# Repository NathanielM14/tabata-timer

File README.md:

tabata-timer-module
***
**Personal Project Description**:

This Tabata Timer Module is used to program calisthenics and any other static/dynamic exercises that are to be done in a specific time interval. The purpose of this timer is to show exercise time, resting time, and sets utilizing finite state machine logic. The module includes 5 fully customizable profiles that are written to the EEPROM to allow for multi-profile saving. Buzzer alerts are given nearing the end of each state to notify user of when they have reached the set amount of time. All components are through-hole and were soldered to the PCB board (Note a simple soldering iron will be required to solder all the through-hole components). Files and descriptions are listed below in the table along with all the required parts for the project.

**Files**:

| File | Description |
| ------- | --------- |
| tabata.kicad_sch | Schematic |
| SSD1306.pretty | SSD1306 Footprint | 
| tabata.kicad_pcb | PCB | 
| tabata_v1.ino | Program |

**Parts List**:
* (1x) 128x64 4-pin SSD1306 OLED (I2C)
* (1x) 5641AS (common anode)
* (4x) Push Button
* (1x) Arduino NANO / NON-OEM equivalent
* (4x) 10kΩ Resistors
* (7x) 220Ω Resistors
* (1x) 330Ω Resistors
* (1x) Passive Buzzer

1.**Schematic**

2. **SSD1306 Footprint**

3. **PCB**

4. **Physical**

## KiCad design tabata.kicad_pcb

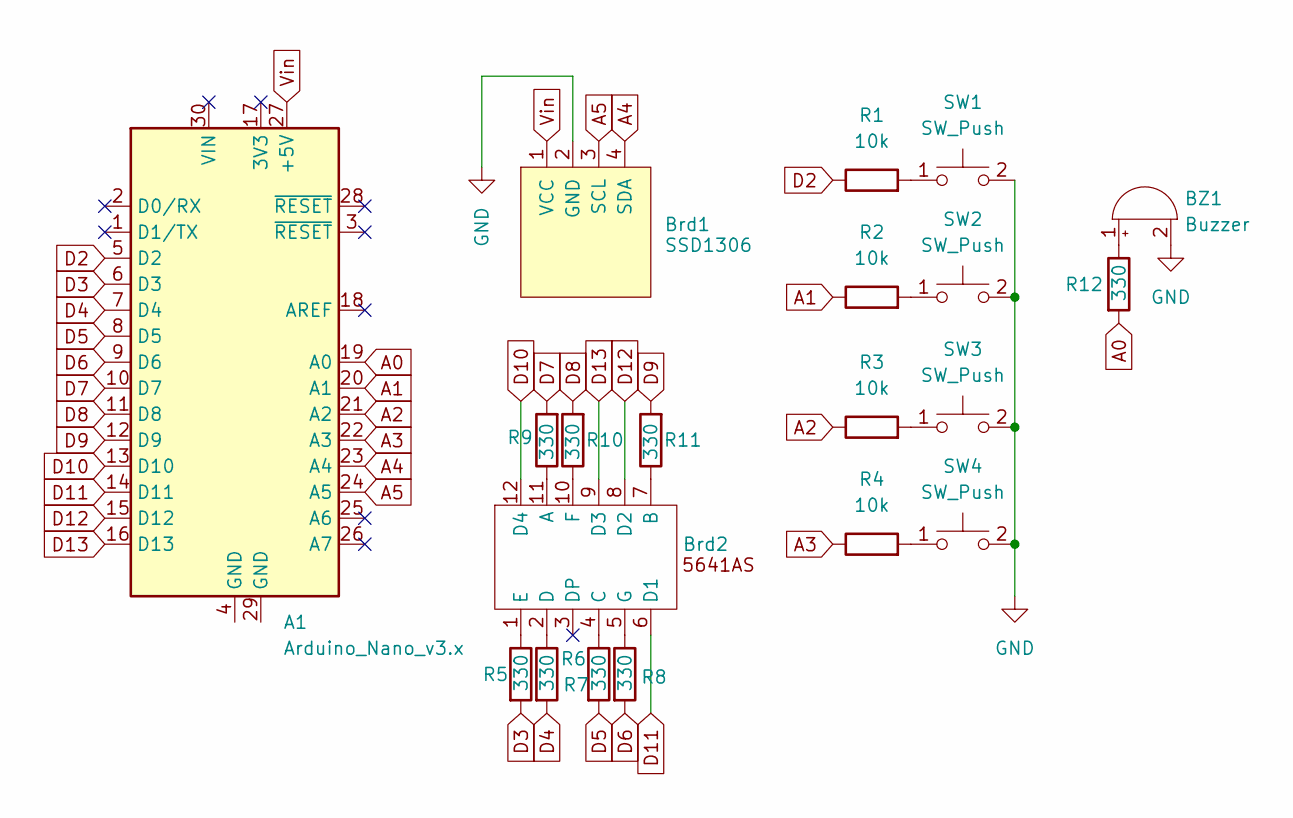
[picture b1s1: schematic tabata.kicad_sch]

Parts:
A1: Arduino_Nano_v3.x; Arduino_Nano
BZ1: Buzzer; Buzzer_12x9.5RM7.6
Brd1: SSD1306; 128x64OLED
Brd2: 5641AS
R1, R2, R3, R4: 10k; R_Axial_DIN0207_L6.3mm_D2.5mm_P7.62mm_Horizontal
R5, R6, R7, R8, R9, R10, R11, R12: 330; R_Axial_DIN0207_L6.3mm_D2.5mm_P7.62mm_Horizontal
SW1, SW2, SW3, SW4: SW_Push; SW_PUSH_6mm_H4.3mm

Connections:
A0: A1.19 (A0), R12.2
A1: A1.20 (A1), R2.1
A2: A1.21 (A2), R3.1
A3: A1.22 (A3), R4.1
A4: A1.23 (A4), Brd1.4 (SDA)
A5: A1.24 (A5), Brd1.3 (SCL)
D2: A1.5 (D2), R1.1
D3: A1.6 (D3), R5.2
D4: A1.7 (D4), R6.2
D5: A1.8 (D5), R7.2
D6: A1.9 (D6), R8.2
D7: A1.10 (D7), R9.2
D8: A1.11 (D8), R10.2
D9: A1.12 (D9), R11.2
D10: A1.13 (D10), Brd2.12 (D4); also elsewhere on the board
D11: A1.14 (D11), Brd2.6 (D1); also elsewhere on the board
D12: A1.15 (D12), Brd2.8 (D2); also elsewhere on the board
D13: A1.16 (D13), Brd2.9 (D3); also elsewhere on the board
GND: A1.4 (GND), A1.29 (GND), BZ1.2 (-), Brd1.2 (GND), SW1.2, SW2.2, SW3.2, SW4.2
unnamed: BZ1.1 (+), R12.1
unnamed 20: Brd2.11 (A), R9.1; also elsewhere on the board
unnamed 21: Brd2.7 (B), R11.1; also elsewhere on the board
unnamed 22: Brd2.4 (C), R7.1; also elsewhere on the board
unnamed 23: Brd2.2 (D), R6.1; also elsewhere on the board
unnamed 24: Brd2.1 (E), R5.1; also elsewhere on the board
unnamed 25: Brd2.10 (F), R10.1; also elsewhere on the board
unnamed 26: Brd2.5 (G), R8.1; also elsewhere on the board
unnamed: R1.2, SW1.1
unnamed: R2.2, SW2.1
unnamed: R3.2, SW3.1
unnamed: R4.2, SW4.1
Vin: A1.27 (+5V), Brd1.1 (VCC)

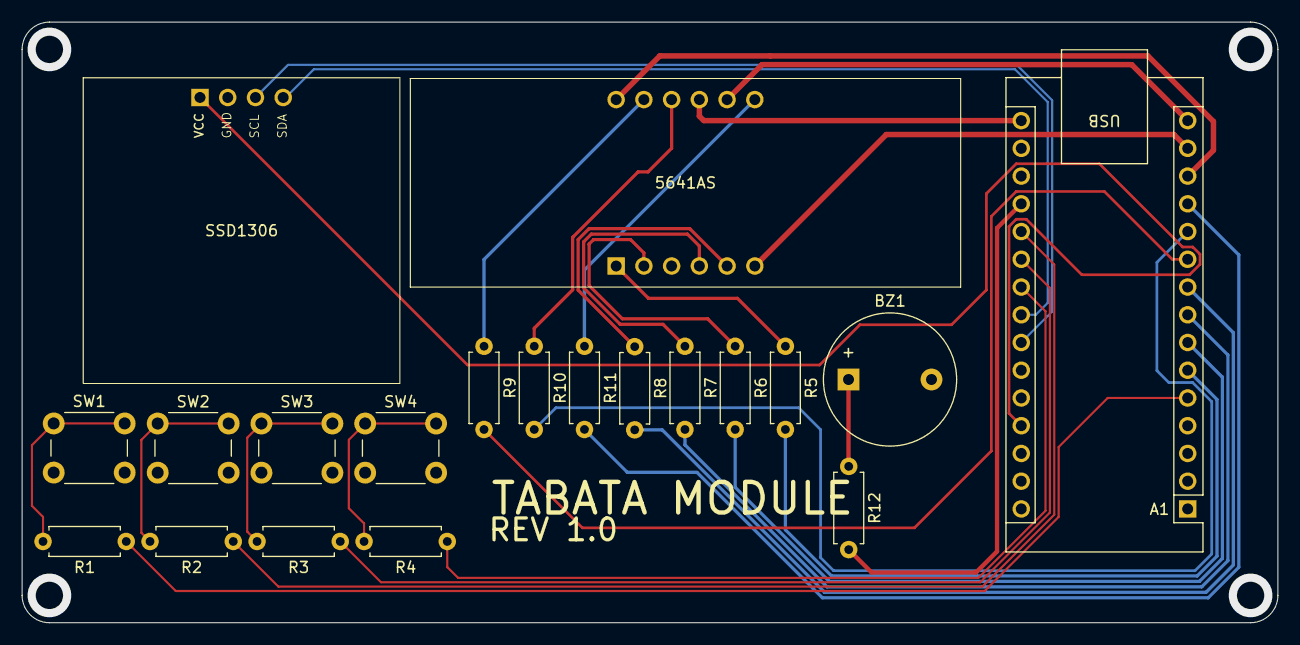
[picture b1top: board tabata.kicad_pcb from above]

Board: 2 copper layers, 115.0 x 55.0 mm, 20 parts (0 on the bottom side), 32 nets.

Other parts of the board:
5641AS: 5641AS

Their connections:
D10: 5641AS.12 (D4); also elsewhere on the board
D11: 5641AS.6 (D1); also elsewhere on the board
D12: 5641AS.8 (D2); also elsewhere on the board
D13: 5641AS.9 (D3); also elsewhere on the board
unnamed 20: 5641AS.11 (A); also elsewhere on the board
unnamed 21: 5641AS.7 (B); also elsewhere on the board
unnamed 22: 5641AS.4 (C); also elsewhere on the board
unnamed 23: 5641AS.2 (D); also elsewhere on the board
unnamed 24: 5641AS.1 (E); also elsewhere on the board
unnamed 25: 5641AS.10 (F); also elsewhere on the board
unnamed 26: 5641AS.5 (G); also elsewhere on the board

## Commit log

2025-07-18 Update tabata_v1.ino
    Made a change so that when DONE state was reached it wouldn't continuously ring the buzzer.
2025-09-13 Create images folder
2025-09-13 Create schematic
